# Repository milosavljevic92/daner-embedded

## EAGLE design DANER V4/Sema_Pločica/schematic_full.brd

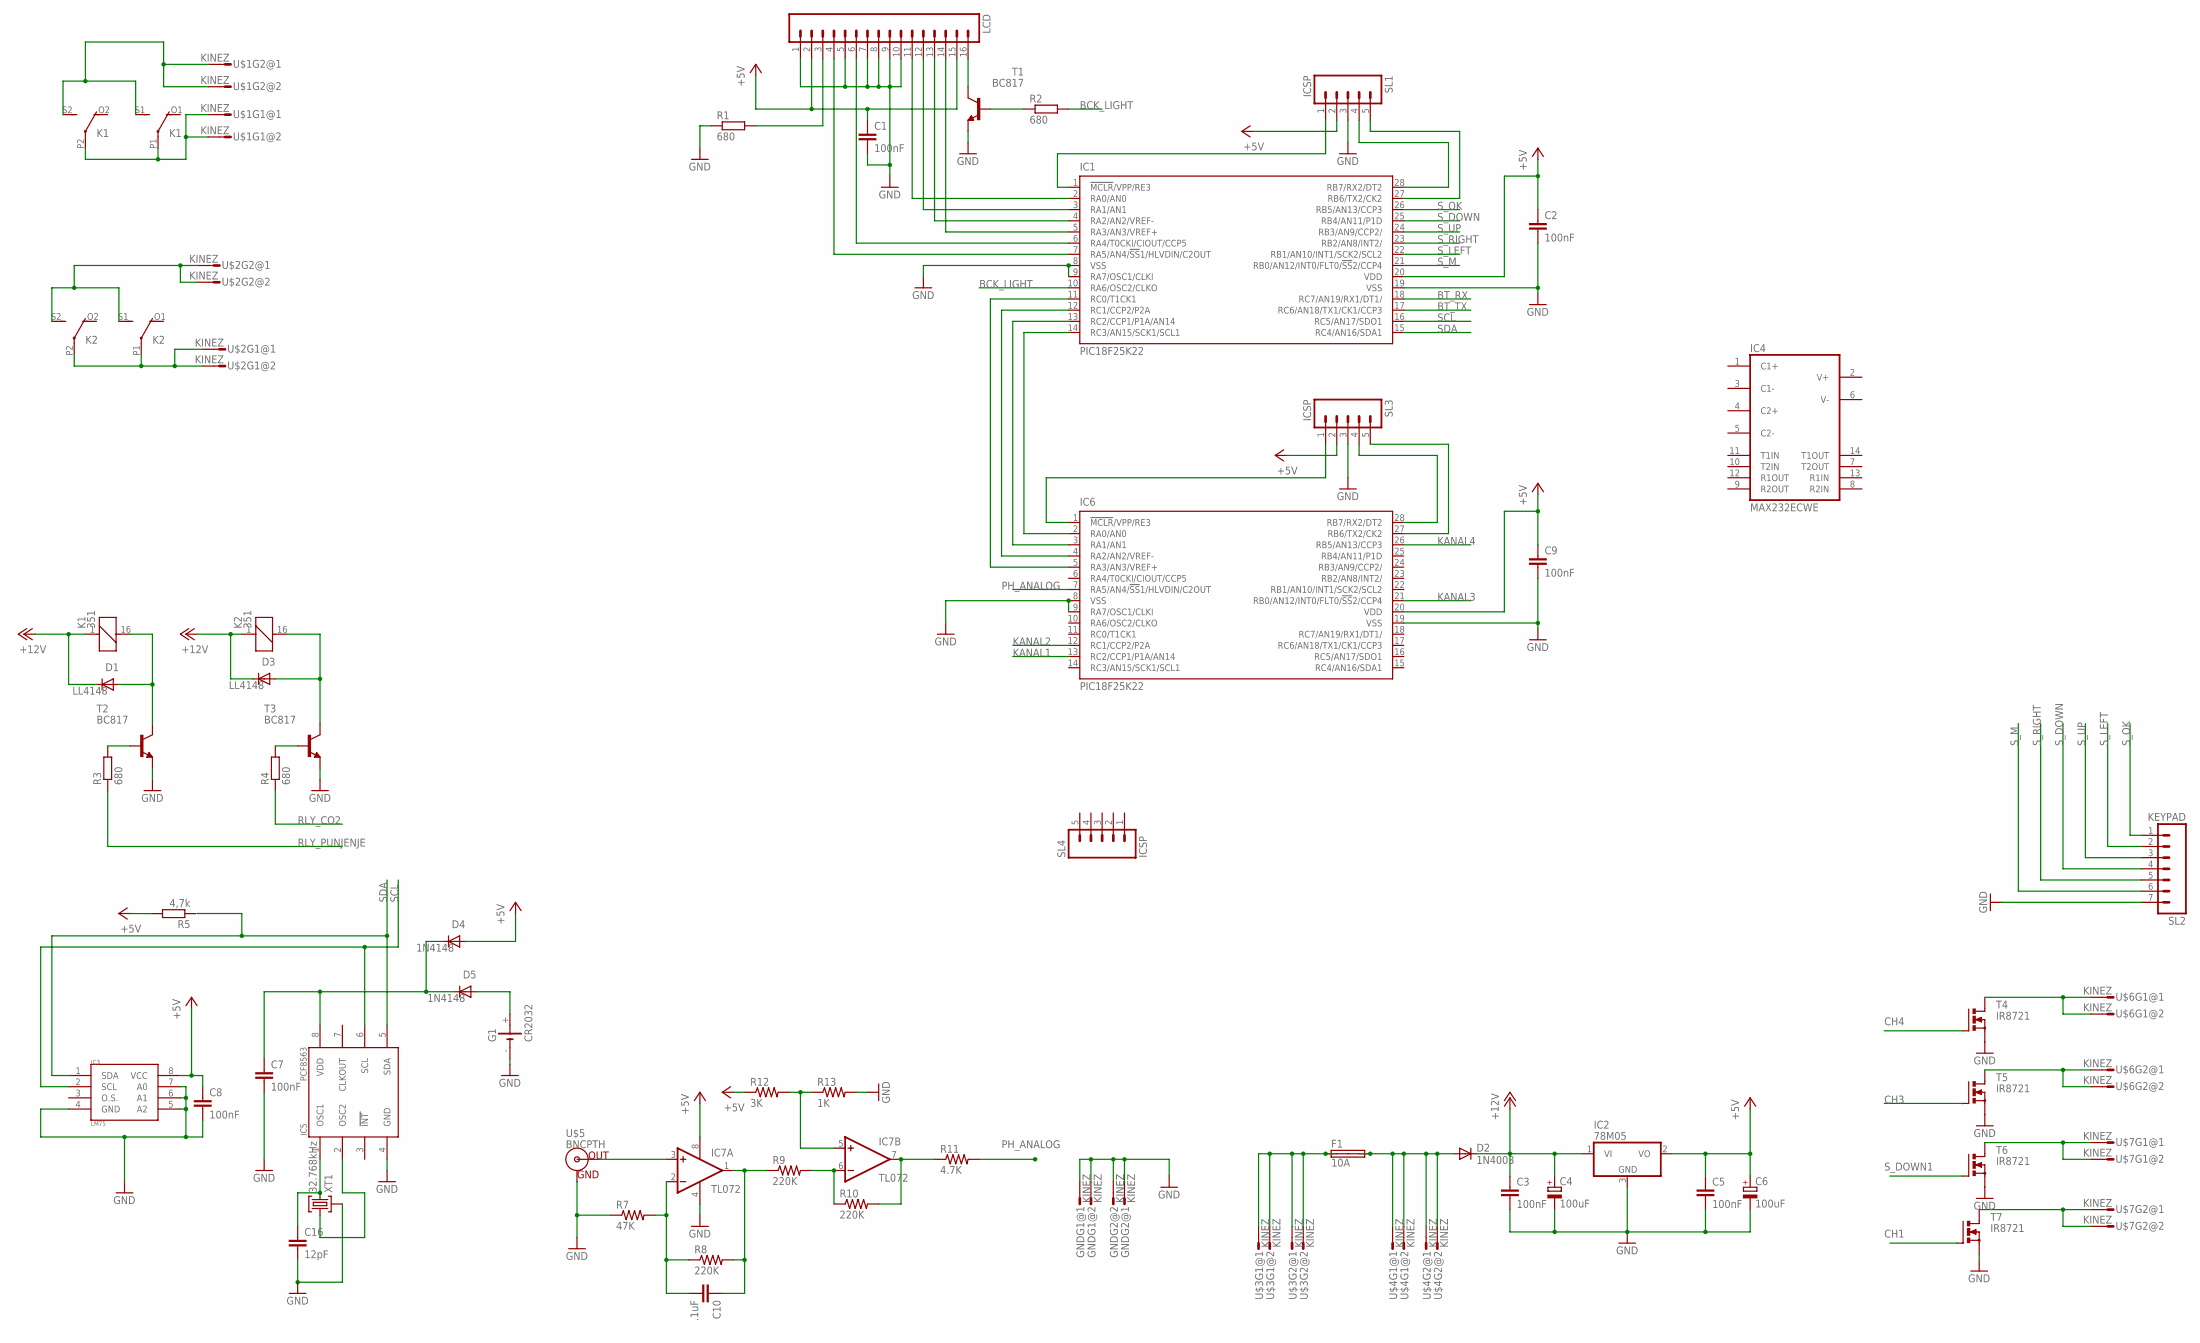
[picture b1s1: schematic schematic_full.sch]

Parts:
C1, C2, C3, C5, C7, C8, C9: 100nF; C0805K
C4: 100uF; E2,5-6E
C6: 100uF; E2,5-6
C10: .1uF; 0805
C16: 12pF; C0805K
D1, D3: LL4148; DO214BA
D2: 1N4003; DO41-10
D4, D5: 1N4148; DO214BA
F1: 10A; SHK20L
G1: CR2032
GND: KINEZ
IC1, IC6: PIC18F25K22; SSOP28
IC2: 78M05; TO252
IC3: LM75; SO08
IC4: MAX232ECWE; SO16L
IC5: PCF8563; SO08
IC7: TL072; SO08
K1, K2: 351
LCD: M16; 16P
R1, R2, R3, R4: 680; M0805
R5: 4,7k; M0805
R7: 47K; 0805
R8, R9, R10: 220K; 0805
R11: 4.7K; 0805
R12: 3K; 0805
R13: 1K; 0805
SL1, SL3, SL4: ICSP; 05P
SL2: KEYPAD; 07PA
T1, T2, T3: BC817; SOT23-BEC
T4, T5, T6, T7: IR8721; TO252
U$1, U$2, U$3, U$4, U$6, U$7: KINEZ
U$5: BNCPTH; BNC
XT1: 32.768kHz; XTMINI

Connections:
+5V: C1.1, C2.1, C5.1, C6.+, C8.1, C9.1, D4.A, IC1.20 (VDD), IC2.2 (VO), IC3.8 (VCC), IC6.20 (VDD), IC7.8 (V+), LCD.2, LCD.15, R5.2, R12.1, SL1.2, SL3.2
+12V: C3.1, C4.+, D1.C, D2.C, D3.C, IC2.1 (VI), K1.1, K2.1
BCK_LIGHT: IC1.10 (RA6/OSC2/CLKO), R2.2
BT_RX: IC1.18 (RC7/AN19/RX1/DT1/)
BT_TX: IC1.17 (RC6/AN18/TX1/CK1/CCP3)
CH1: T7.1 (G)
CH3: T5.1 (G)
CH4: T4.1 (G)
GND: C1.2, C2.2, C3.2, C4.-, C5.2, C6.-, C7.2, C8.2, C9.2, C16.2, G1.-, GND.1, GND.2, GND.3, GND.4, IC1.8 (VSS), IC1.9 (RA7/OSC1/CLKI), IC1.19 (VSS), IC2.3 (GND), IC3.4 (GND), IC3.5 (A2), IC3.6 (A1), IC3.7 (A0), IC4.15 (GND), IC5.4 (GND), IC6.8 (VSS), IC6.9 (RA7/OSC1/CLKI), IC7.4 (V-), LCD.1, LCD.5, LCD.7, LCD.8, LCD.9, LCD.10, R1.1, R7.1, R13.2, SL1.3, SL2.7, SL3.3, T1.E, T2.E, T3.E, T4.3 (S), T5.3 (S), T6.3 (S), T7.3 (S), U$5.GND, XT1.P$3 (3)
KANAL1: IC6.13 (RC2/CCP1/P1A/AN14)
KANAL2: IC6.12 (RC1/CCP2/P2A)
KANAL3: IC6.21 (RB0/AN12/INT0/FLT0/!SS!2/CCP4)
KANAL4: IC6.26 (RB5/AN13/CCP3)
unnamed: D5.A, G1.+
unnamed: K1.S1 (S), K1.S2 (S), U$1.3, U$1.4
unnamed: K2.P1, K2.P2, U$2.1, U$2.2
unnamed: F1.1A, F1.1B, U$3.1, U$3.2, U$3.3, U$3.4
unnamed: D2.A, F1.2A, F1.2B, U$4.1, U$4.2, U$4.3, U$4.4
unnamed: IC6.27 (RB6/TX2/CK2), SL3.5
unnamed: IC6.28 (RB7/RX2/DT2), SL3.4
unnamed: IC5.2 (OSC2), XT1.P$1 (1)
unnamed: IC6.1 (!MCLR!/VPP/RE3), SL3.1
unnamed: IC1.14 (RC3/AN15/SCK1/SCL1), IC6.2 (RA0/AN0)
unnamed: IC1.13 (RC2/CCP1/P1A/AN14), IC6.3 (RA1/AN1)
unnamed: C7.1, D4.C, D5.C, IC5.8 (VDD)
unnamed: IC1.2 (RA0/AN0), LCD.11
unnamed: IC1.3 (RA1/AN1), LCD.12
unnamed: IC1.4 (RA2/AN2/VREF-), LCD.13
unnamed: IC1.5 (RA3/AN3/VREF+), LCD.14
unnamed: IC1.6 (RA4/T0CKI/CIOUT/CCP5), LCD.6
unnamed: T5.2 (D), U$6.3, U$6.4
unnamed: IC1.7 (RA5/AN4/!SS!1/HLVDIN/C2OUT), LCD.4
unnamed: LCD.3, R1.2
unnamed: T6.2 (D), U$7.1, U$7.2
unnamed: T7.2 (D), U$7.3, U$7.4
unnamed: D1.A, K1.16 (2), T2.C
unnamed: C16.1, IC5.1 (OSC1), XT1.P$2 (2)
unnamed: IC1.12 (RC1/CCP2/P2A), IC6.4 (RA2/AN2/VREF-)
unnamed: D3.A, K2.16 (2), T3.C
unnamed: LCD.16, T1.C
unnamed: R4.2, T3.B
unnamed: R3.2, T2.B
unnamed: K1.P1, K1.P2, U$1.1, U$1.2
unnamed: IC1.11 (RC0/T1CK1), IC6.5 (RA3/AN3/VREF+)
unnamed: R2.1, T1.B
unnamed: IC7.5 (+IN), R12.2, R13.1
unnamed: IC7.7 (OUT), R10.2, R11.1
unnamed: IC1.28 (RB7/RX2/DT2), SL1.4
unnamed: IC1.27 (RB6/TX2/CK2), SL1.5
unnamed: IC7.6 (-IN), R9.2, R10.1
unnamed: IC7.3 (+IN), U$5.S (OUT)
unnamed: T4.2 (D), U$6.1, U$6.2
unnamed: C10.1, IC7.1 (OUT), R8.2, R9.1
unnamed: C10.2, IC7.2 (-IN), R7.2, R8.1
unnamed: IC1.1 (!MCLR!/VPP/RE3), SL1.1
PH_ANALOG: IC6.7 (RA5/AN4/!SS!1/HLVDIN/C2OUT), R11.2
RLY_CO2: R4.1
RLY_PUNJENJE: R3.1
SCL: IC1.16 (RC5/AN17/SDO1), IC3.2 (SCL), IC5.6 (SCL)
SDA: IC1.15 (RC4/AN16/SDA1), IC3.1 (SDA), IC5.5 (SDA)
SWITCH2_IN: K2.S1 (S), K2.S2 (S), U$2.3, U$2.4
S_DOWN: IC1.25 (RB4/AN11/P1D), SL2.4
S_DOWN1: T6.1 (G)
S_LEFT: IC1.22 (RB1/AN10/INT1/SCK2/SCL2), SL2.2
S_M: IC1.21 (RB0/AN12/INT0/FLT0/!SS!2/CCP4), SL2.6
S_OK: IC1.26 (RB5/AN13/CCP3), SL2.1
S_RIGHT: IC1.23 (RB2/AN8/INT2/), SL2.5
S_UP: IC1.24 (RB3/AN9/CCP2/), SL2.3
VCC: IC4.16 (VCC)
VSS: IC6.19 (VSS)

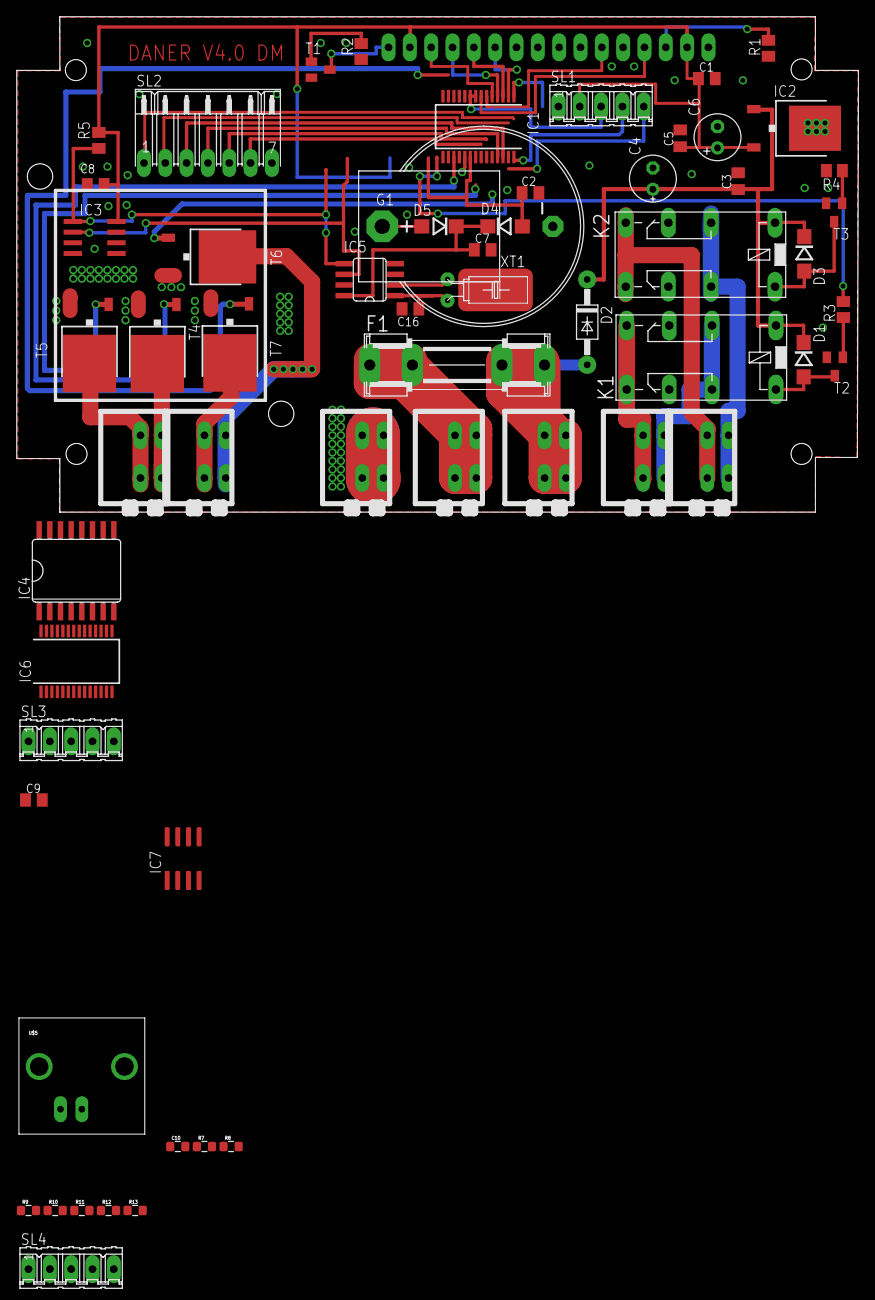
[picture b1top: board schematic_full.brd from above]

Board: 2 copper layers, 100.3 x 59.0 mm, 60 parts (1 on the bottom side), 56 nets.

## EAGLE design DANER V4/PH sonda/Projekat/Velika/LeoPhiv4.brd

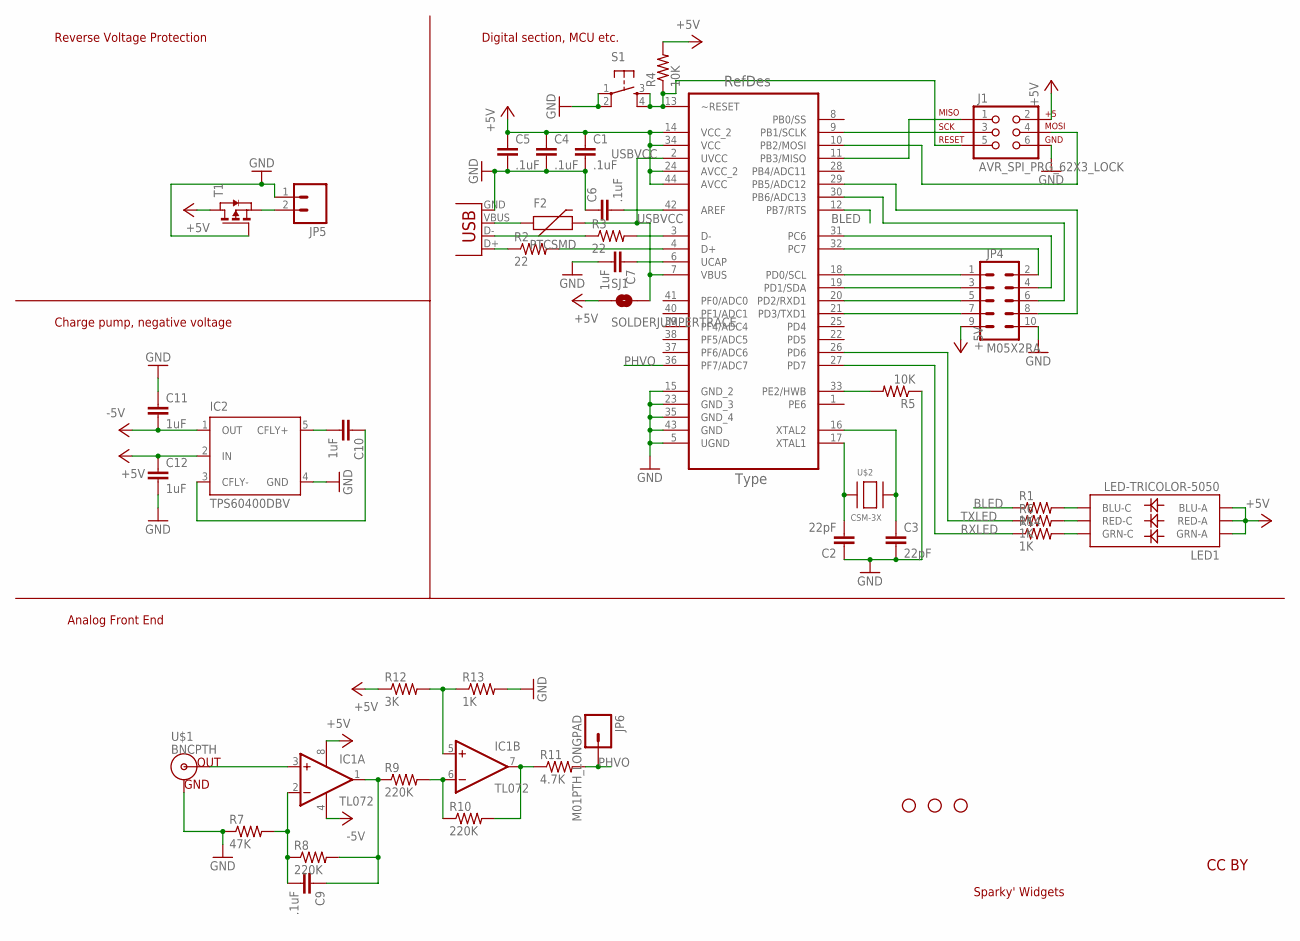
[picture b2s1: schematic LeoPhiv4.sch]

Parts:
C1, C4, C5, C6, C9: .1uF; 0805
C2, C3: 22pF; 0805
C7, C10, C11, C12: 1uF; 0805
F2: PTCSMD; PTC-1206
IC1: TL072; SO08
IC2: TPS60400DBV; SOT23-DBV
J1: AVR_SPI_PRG_62X3_LOCK; 2X3_LOCK
JP1, JP2, JP3: STAND-OFF
JP4: M05X2RA; 2X5-RA
JP5: M02POLAR; MOLEX-1X2
JP6: M01PTH_LONGPAD; 1X01_LONGPAD
LED1: LED-TRICOLOR-5050
R1, R6, R13, R14: 1K; 0805
R2, R3: 22; 0805
R4, R5: 10K; 0805
R7: 47K; 0805
R8, R9, R10: 220K; 0805
R11: 4.7K; 0805
R12: 3K; 0805
S1: TAC_SWITCHSMD; TACTILE_SWITCH_SMD
SJ1: SOLDERJUMPERTRACE; SJ_2S-TRACE
T1: PMOSSOT23; SOT-23
U1: ATMEGA32U4-AU; QFP80P1200X1200X120-44N
U$1: BNCPTH; BNC
U$2: CSM-3X; XTALCSM3X
X1: USBSMD; USB-MINIB

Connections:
+5V: C1.1, C4.1, C5.1, C12.1, IC1.8 (V+), IC2.2 (IN), J1.2, JP4.9, LED1.1 (GRN-A), LED1.2 (RED-A), LED1.3 (BLU-A), R4.2, R12.1, SJ1.1, T1.1 (D), U1.14 (VCC_2), U1.24 (AVCC_2), U1.34 (VCC), U1.44 (AVCC)
-5V: C11.2, IC1.4 (V-), IC2.1 (OUT)
AREF: C6.2, U1.42 (AREF)
BLED: R1.1, U1.12 (PB7/RTS)
GND: C1.2, C2.1, C3.2, C4.2, C5.2, C6.1, C7.2, C11.1, C12.2, IC2.4 (GND), J1.6, JP4.10, JP5.1, R5.1, R7.1, R13.2, S1.1, S1.2, T1.3 (G), U1.5 (UGND), U1.15 (GND_2), U1.23 (GND_3), U1.35 (GND_4), U1.43 (GND), U$1.GND, X1.GND
unnamed: IC1.5 (+IN), R12.2, R13.1
unnamed: IC1.7 (OUT), R10.2, R11.1
unnamed: IC1.6 (-IN), R9.2, R10.1
unnamed: C2.2, U1.17 (XTAL1), U$2.1
unnamed: JP4.2, U1.32 (PC7)
unnamed: C3.1, U1.16 (XTAL2), U$2.2
unnamed: IC1.3 (+IN), U$1.S (OUT)
unnamed: J1.3, U1.9 (PB1/SCLK)
unnamed: C9.2, IC1.2 (-IN), R7.2, R8.1
unnamed: C9.1, IC1.1 (OUT), R8.2, R9.1
unnamed: R5.2, U1.33 (PE2/HWB)
unnamed: JP5.2, T1.2 (S)
unnamed: R3.1, X1.D-
unnamed: R3.2, U1.3 (D-)
unnamed: R2.1, X1.D+
unnamed: R2.2, U1.4 (D+)
unnamed: C7.1, U1.6 (UCAP)
unnamed: J1.4, U1.10 (PB2/MOSI)
unnamed: J1.1, U1.11 (PB3/MISO)
unnamed: F2.1, X1.VBUS
unnamed: J1.5, R4.1, S1.3, S1.4, U1.13 (~RESET)
unnamed: C10.1, IC2.3 (CFLY-)
unnamed: C10.2, IC2.5 (CFLY+)
unnamed: JP4.1, U1.18 (PD0/SCL)
unnamed: JP4.3, U1.19 (PD1/SDA)
unnamed: JP4.5, U1.20 (PD2/RXD1)
unnamed: JP4.7, U1.21 (PD3/TXD1)
unnamed: JP4.4, U1.31 (PC6)
unnamed: JP4.6, U1.30 (PB6/ADC13)
unnamed: JP4.8, U1.29 (PB5/ADC12)
unnamed: LED1.4 (BLU-C), R1.2
unnamed: LED1.5 (RED-C), R6.2
unnamed: LED1.6 (GRN-C), R14.2
PHVO: JP6.1, R11.2, U1.36 (PF7/ADC7)
RXLED: R14.1, U1.27 (PD7)
TXLED: R6.1, U1.26 (PD6)
USBVCC: F2.2, SJ1.2, U1.2 (UVCC), U1.7 (VBUS)

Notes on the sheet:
CC BY
Reverse Voltage Protection
Charge pump, negative voltage
Analog Front End
Digital section, MCU etc.
Sparky' Widgets

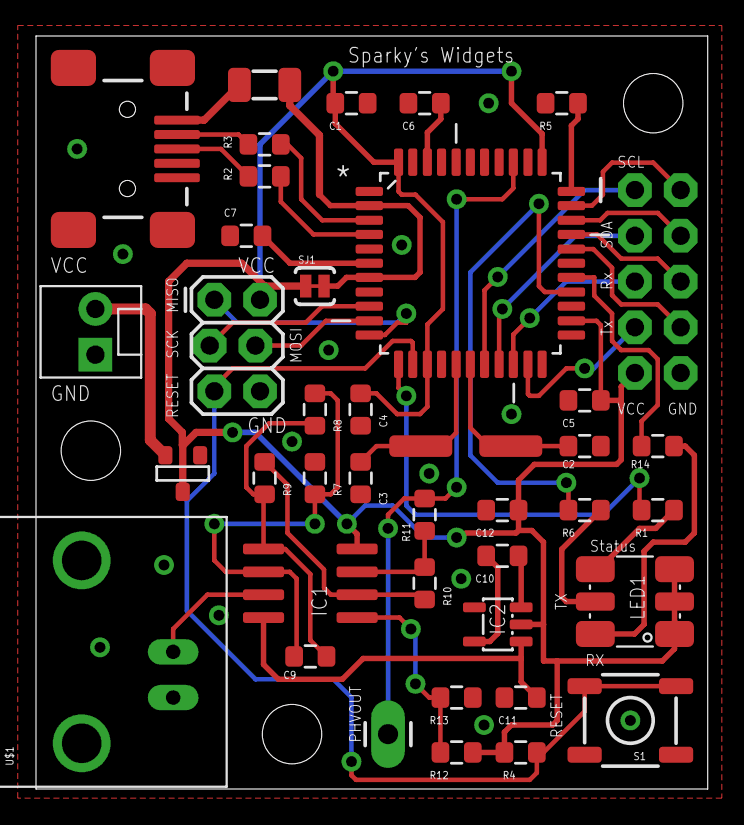
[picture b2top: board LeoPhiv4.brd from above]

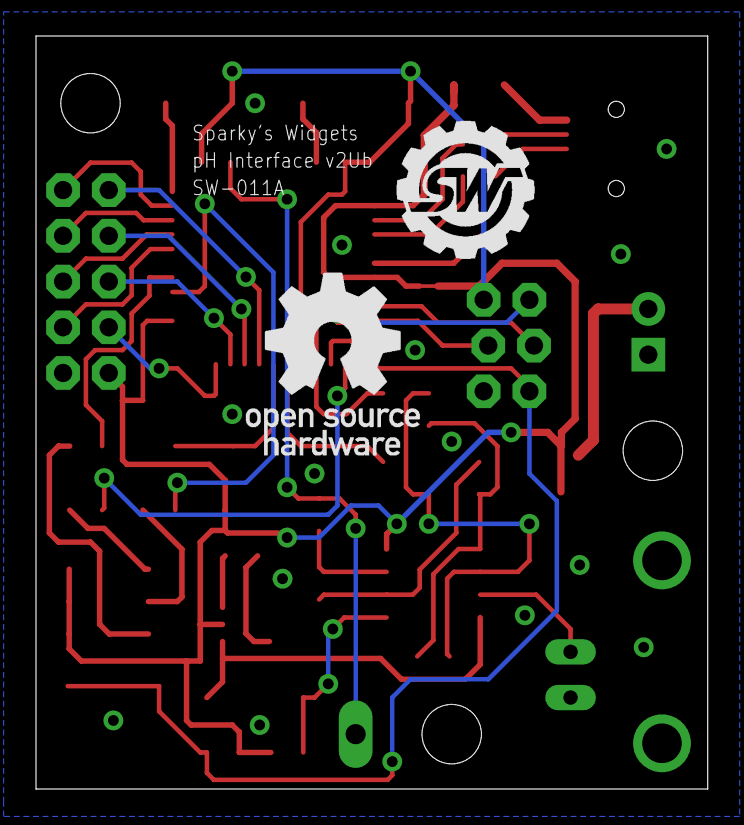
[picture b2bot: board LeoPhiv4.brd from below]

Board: 2 copper layers, 37.3 x 41.8 mm, 45 parts (2 on the bottom side), 42 nets.

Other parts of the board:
U$3: SWPCBLOGOMED
U$4: OSHWLOGO

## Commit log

2022-05-22 [CLEANUP] Project cleanup
